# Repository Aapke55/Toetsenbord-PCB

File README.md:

# Toetsenbord PCB
 Toetsenbordje dabij

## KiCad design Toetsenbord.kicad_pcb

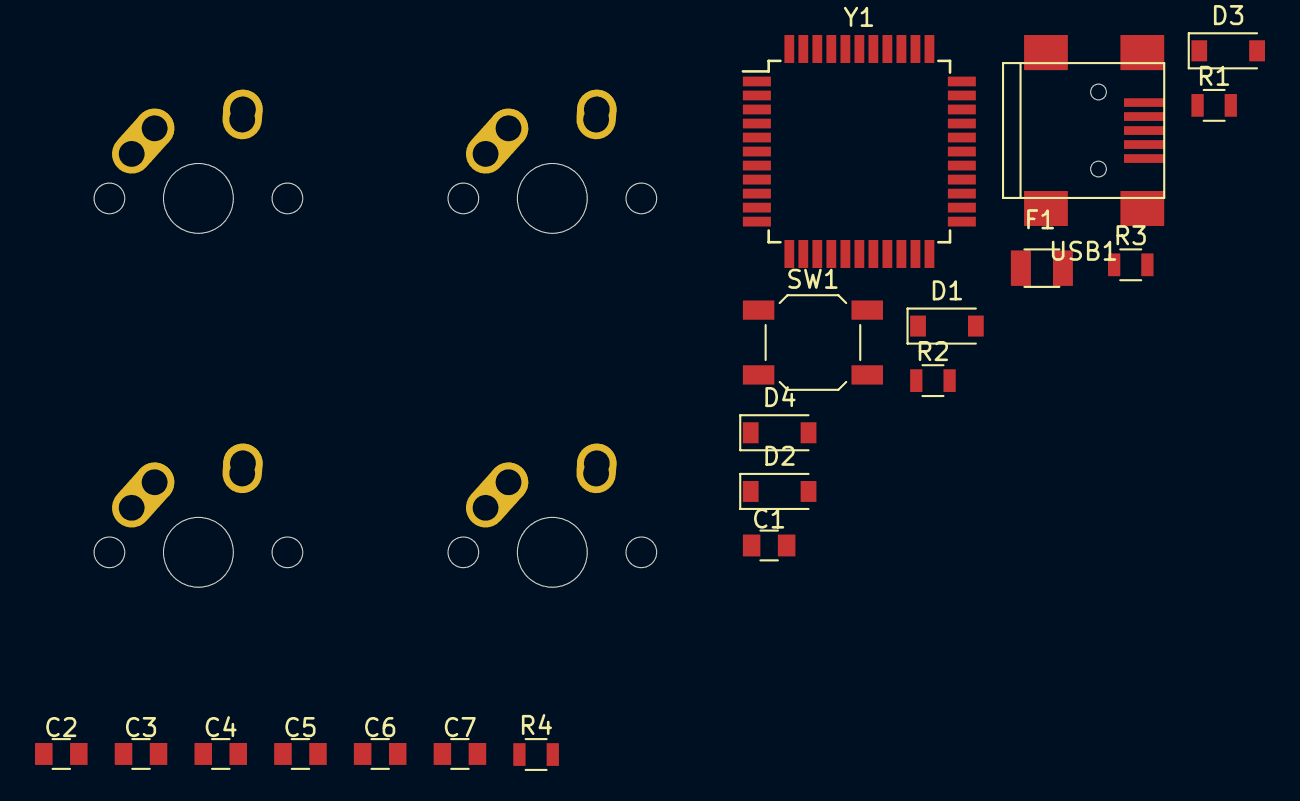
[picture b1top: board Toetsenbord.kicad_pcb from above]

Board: 2 copper layers, 23 parts (0 on the bottom side), 16 nets, no tracks yet.

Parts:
C1, C4, C5: 0.1uF; C_0805
C2, C3: 22pF; C_0805
C6: C_Small; C_0805
C7: 10uF; C_0805
D1, D2, D3, D4: D_Small; D_SOD-123
F1: 500mA; Fuse_SMD1206_Reflow
MX1, MX2, MX3, MX4: MX-NoLED; MX-1U-NoLED
R1, R2: 22; R_0805
R3, R4: 10k; R_0805
SW1: SW_Push; SW_SPST_SKQG
USB1: Molex-0548190589; USB_Mini-B
Y1: 16MHz; LQFP-44_10x10mm_Pitch0.8mm

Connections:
+5V: C1.1, C4.1, C5.1, C7.1, F1.1, R3.2
COL0: MX1.1, MX2.1
COL1: MX3.1, MX4.1
D+: R2.2, USB1.3
D-: R1.2, USB1.4
GND: C1.2, C2.1, C3.1, C4.2, C5.2, C6.2, C7.2, R4.1, SW1.1, USB1.1, Y1.2, Y1.4
unnamed: C2.2, Y1.1
unnamed: C3.2, Y1.3
unnamed: D1.2, MX1.2
unnamed: D2.2, MX2.2
unnamed: D3.2, MX3.2
unnamed: D4.2, MX4.2
unnamed: R3.1, SW1.2
ROW0: D1.1, D3.1
ROW1: D2.1, D4.1
VCC: F1.2, USB1.5

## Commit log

2019-07-03 Add submodules
2019-07-03 Footprint libraries
    Opla
2019-07-03 Update fp-lib-table
2019-07-03 Schemas
